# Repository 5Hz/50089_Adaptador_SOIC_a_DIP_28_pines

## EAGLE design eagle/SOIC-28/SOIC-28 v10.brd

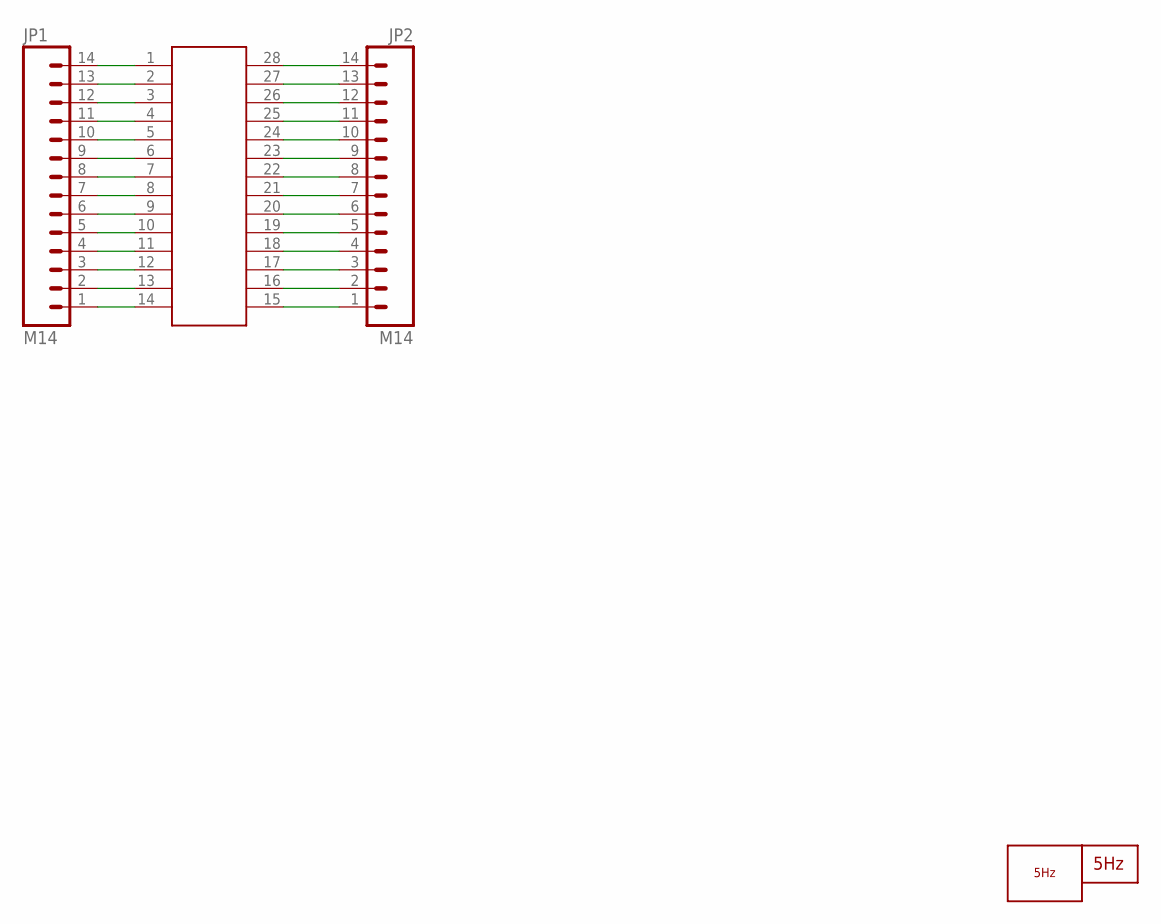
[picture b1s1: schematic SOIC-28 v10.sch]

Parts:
JP1, JP2: M14; 1X14
LOGO1: LOGO_5HZ_MAIN_5MM; 5HZ_LOGO_MAIN_5MM
U$1: SOIC-28SOIC-28; SOIC-28
U$2: LOGO2_SILK10MM; LOGO2_10MM

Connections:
unnamed: JP1.1, U$1.14
unnamed: JP1.2, U$1.13
unnamed: JP1.3, U$1.12
unnamed: JP1.4, U$1.11
unnamed: JP1.5, U$1.10
unnamed: JP1.6, U$1.9
unnamed: JP1.7, U$1.8
unnamed: JP1.8, U$1.7
unnamed: JP1.9, U$1.6
unnamed: JP1.10, U$1.5
unnamed: JP1.11, U$1.4
unnamed: JP1.12, U$1.3
unnamed: JP1.13, U$1.2
unnamed: JP1.14, U$1.1
unnamed: JP2.1, U$1.15
unnamed: JP2.2, U$1.16
unnamed: JP2.3, U$1.17
unnamed: JP2.4, U$1.18
unnamed: JP2.5, U$1.19
unnamed: JP2.6, U$1.20
unnamed: JP2.7, U$1.21
unnamed: JP2.8, U$1.22
unnamed: JP2.9, U$1.23
unnamed: JP2.10, U$1.24
unnamed: JP2.11, U$1.25
unnamed: JP2.12, U$1.26
unnamed: JP2.13, U$1.27
unnamed: JP2.14, U$1.28

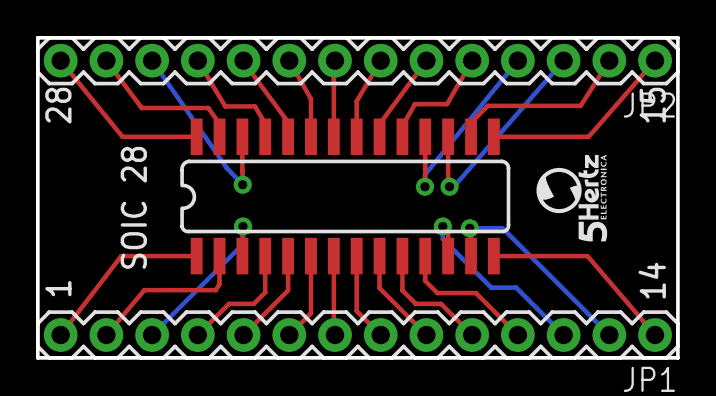
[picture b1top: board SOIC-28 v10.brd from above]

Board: 2 copper layers, 35.6 x 17.8 mm, 5 parts (1 on the bottom side), 28 nets.

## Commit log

2014-01-13 creación

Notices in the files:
parts and their libraries:
SparkFun: Licensing: CC v3.0 Share-Alike You are welcome to use this library for commercial purposes.
